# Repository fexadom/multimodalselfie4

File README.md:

# MultimodalSelfie v4
The MultimodalSelfie is a personal multimodal recording device designed for traditional classrooms. The device, owned and operated by the student, sits on top of her desk while recording video, audio, and notes during a class session (as seen in the concept image below); effectively taking a "selfie" of her learning experience.

## Design
This repository contains all the necessary information to construct and test the fourth version of the MultimodalSelfie device (MMSv4 for short). The MMSv4 is based on the [Raspberry Pi Zero W](https://www.raspberrypi.org/products/raspberry-pi-zero-w/) a stripped down version of the Raspberry Pi with wireless connectivity.

Front View | Components | Functionality
--- | --- | ---
 |  | 

### Hardware components
The MMSv4 was built using the following components:

Component | Description | Notes
--- | --- | ---
Raspberry Pi Zero W | 1GHz 64-bit, single-core ARMv8 CPU, 512 MB RAM | 32 GB micro SD
Raspberry Pi Camera | Camera Rev 1.3, 5 megapixeles | Capable of 1080p HD video recording at 30fps
Smart Pen | Equil SmartPen2 | [Manufacturer website](https://www.myequil.com/smartpen2/)
3D Printed Case | Three parts printed using PLA | [STLs](/case)
Pihat | Printed Circuit Board that expands the Raspberry Pi capabilities, it connects to the 40 GPIO port. It has a swith, a LED, and two digital microphones. | [Design files](/pihat)
2 x digital MEMS microphones | The two ICS43432 mics are surface mounted on the Pihat and capable of stereo recording. | [Manufacturer website](https://www.invensense.com/products/digital/ics-43432/)
LiPo battery charger  | SparkFun LiPo Charger Basic - Micro-USB | [Manufacturer website](https://www.sparkfun.com/products/10217)
LiPo battery  | 2000mAh Lithium Ion battery | [Manufacturer website](https://www.sparkfun.com/products/13855)

### Software components
The operating system used is [Raspbian Stretch Lite](https://www.raspberrypi.org/downloads/raspbian/) (Release date 2017-11-29). Video and audio are captured and synchronized using **ffmpeg** and overall synchronization is done with Node-Red:
* [Node-Red flows](/synchronization-software)

## Dependencies
After installing Raspbian Stretch Lite (avoid installing any GUI and unnecessary packages) update as needed with:
```bash
sudo apt-get update
sudo apt-get upgrade
```
then install the following dependencies:

### ffmpeg
For best results, install ffmpeg and its dependencies from the official repository:
```bash
sudo apt-get install ffmpeg
```

### Node-RED
Node-RED is pre-installed in Raspbian Stretch, to enable it:
```bash
sudo systemctl enable nodered.service
```

### Equil
The Equil driver for the SmartPen2 requires Java, to install:
```bash
sudo apt-get install jsvc
```
## Configuration Notes
To use the camera port it is necessary to enable it at boot time, run:
```bash
sudo raspi-config
```
and enable the camera. To map the camera driver to /dev/video0 add this line to /etc/rc.local:
```bash
modprobe bcm2835-v4l2
```
### Installation of synchronization software
Install the contents of the [synchronization software](/synchronization-software) in the folder /opt/recording:
```bash
git clone https://github.com/fexadom/multimodalselfie4.git
cd multimodalselfie4
sudo mv synchronization-software /opt/recording
```
* Copy /opt/recording/node-red/settings.js to ~/.node-red/
* Copy the directory /opt/recording/node-red/node_modules/file-exists to ~/.node-red/node_modules/
* Create a directory "data" in /opt/recording
* Restart the system

### Configure Equil software
Open Equil.sh in /opt/recording/scripts/ and modify as needed:
```bash
JAVA_HOME: Location JAVA JRE
EXEC: Location JSVC
```
### Installation of ICS43432 driver
Use this post: [Add an I2S mic using device tree & simple-audio-card](https://www.raspberrypi.org/forums/viewtopic.php?f=44&t=173640) to install the driver for the ICS43432 digital microphones.

### Configure web server Lighttpd
The web server [Lighttpd](https://www.lighttpd.net/) is necessary to extract all recorded software. To install first remove Apache httpd if installed, then install **lighthttpd** from the official repositoty and enable the service:
```bash
sudo apt-get remove apache2
sudo apt-get install lighttpd
sudo systemctl enable lighttpd.service
```

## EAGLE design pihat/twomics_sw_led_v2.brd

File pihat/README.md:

# Design files for pihat MultimodalSelfie version 4
The pihat for the MMSv4 is a two-layer PCB that connects to the 40-pin GPIO interface of the Raspberry Pi Zero W. It provides the following functionality to the MMSv4:
* Ready LED on GPIO 02
* Push button on GPIO 03
* Two digital MEMS ICS43432 microphones multiplexed together and connected to I2S interface of the Raspberry Pi (GPIO 18-20)

The design files in this repository were made in Eagle v8.

Pihat on device | Pihat front | Pihat back
--- | --- | ---
 |  |

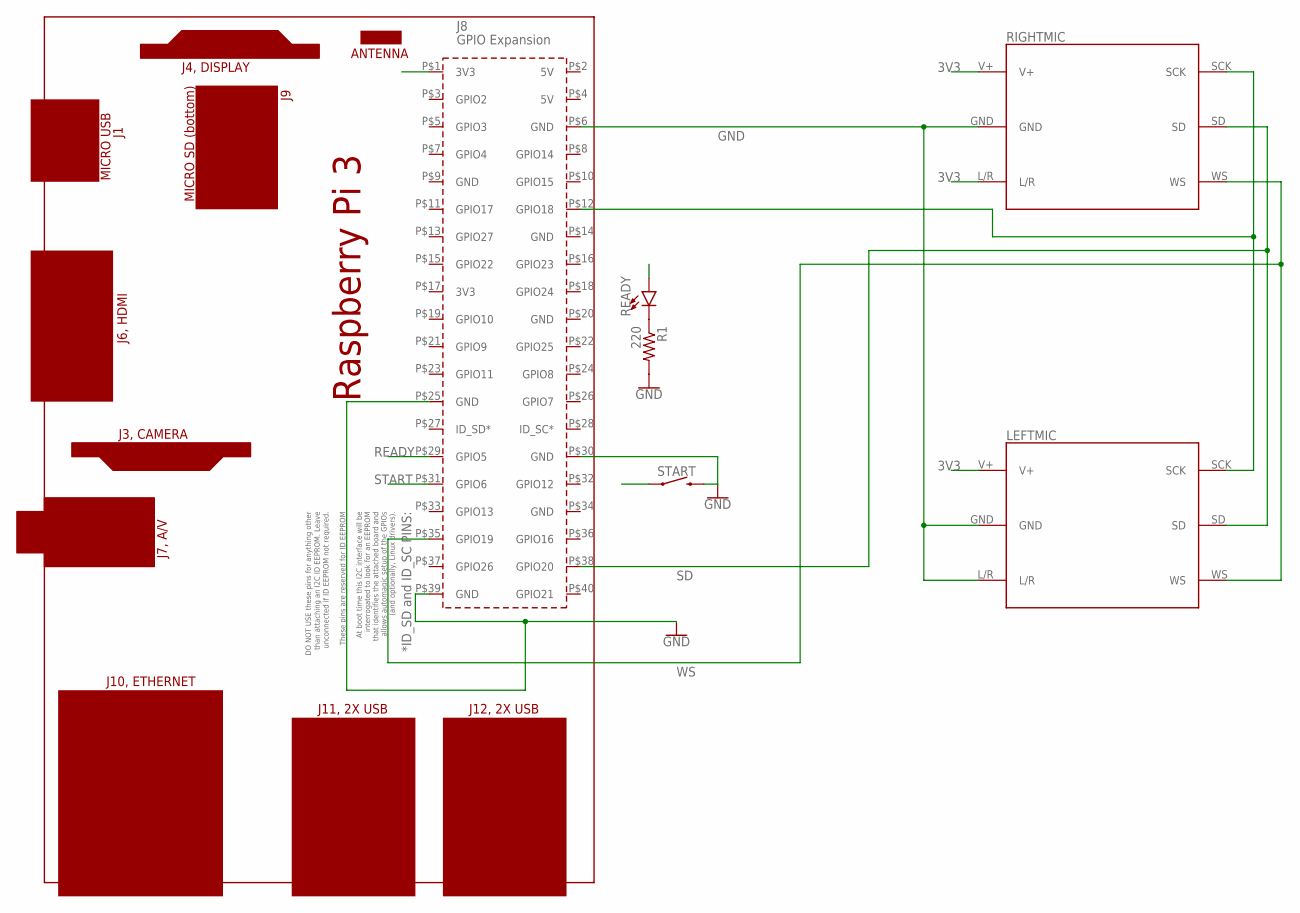
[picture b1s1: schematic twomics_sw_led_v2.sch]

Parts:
LEFTMIC: EMMIC-ICS43432; PTH
PCB1: RPI3_40_PIN; 40_PIN
R1: 220; 0207/7
READY: LED3MM; LED_3MM
RIGHTMIC: EMMIC-ICS43432; PTH
START: MOMENTARY-SWITCH-SPST-PTH-6.0MM; TACTILE_SWITCH_PTH_6.0MM

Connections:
3V3: LEFTMIC.V+, PCB1.P$1 (3V3), RIGHTMIC.L/R, RIGHTMIC.V+
GND: LEFTMIC.GND, LEFTMIC.L/R, PCB1.P$6 (GND), PCB1.P$25 (GND), PCB1.P$30 (GND), PCB1.P$39 (GND), R1.2, RIGHTMIC.GND, START.3 (2)
unnamed: R1.1, READY.K (C)
READY: PCB1.P$29 (GPIO5), READY.A
SCK: LEFTMIC.SCK, PCB1.P$12 (GPIO18), RIGHTMIC.SCK
SD: LEFTMIC.SD, PCB1.P$38 (GPIO20), RIGHTMIC.SD
START: PCB1.P$31 (GPIO6), START.1
WS: LEFTMIC.WS, PCB1.P$35 (GPIO19), RIGHTMIC.WS

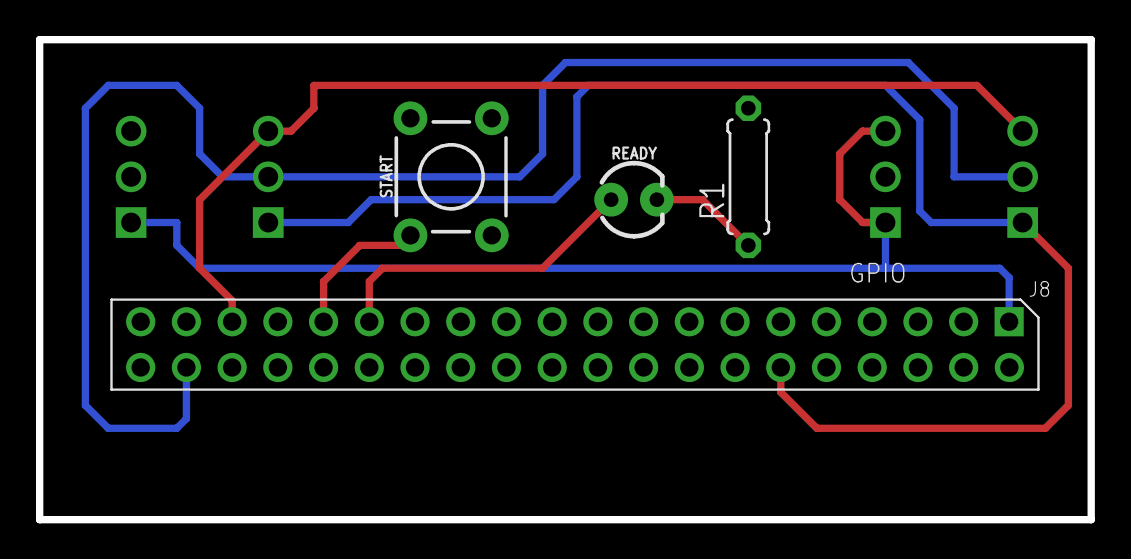
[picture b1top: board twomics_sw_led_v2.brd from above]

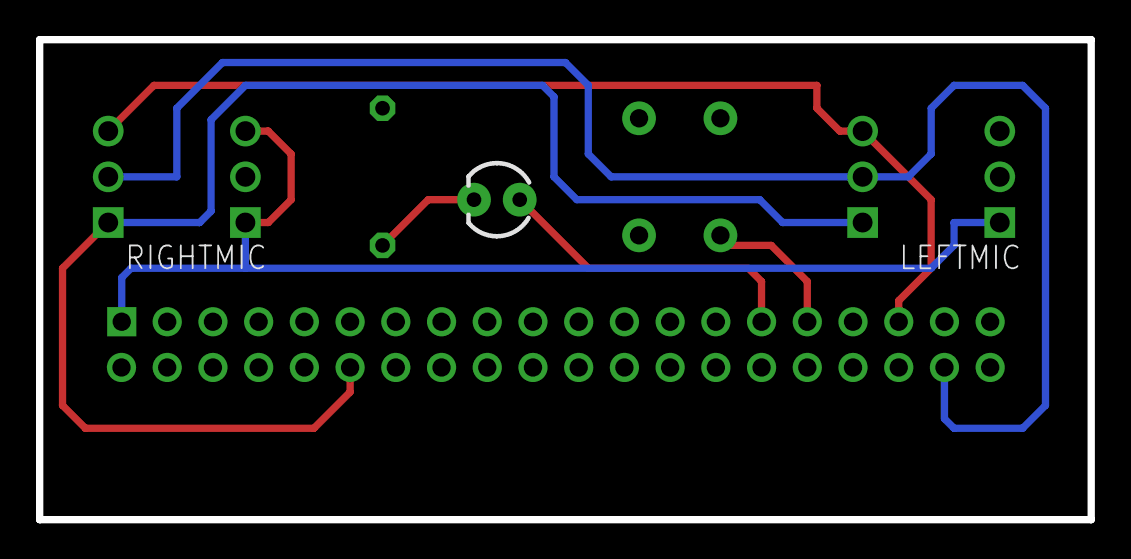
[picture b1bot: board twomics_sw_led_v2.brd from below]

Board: 2 copper layers, 58.4 x 26.7 mm, 6 parts (2 on the bottom side), 8 nets.

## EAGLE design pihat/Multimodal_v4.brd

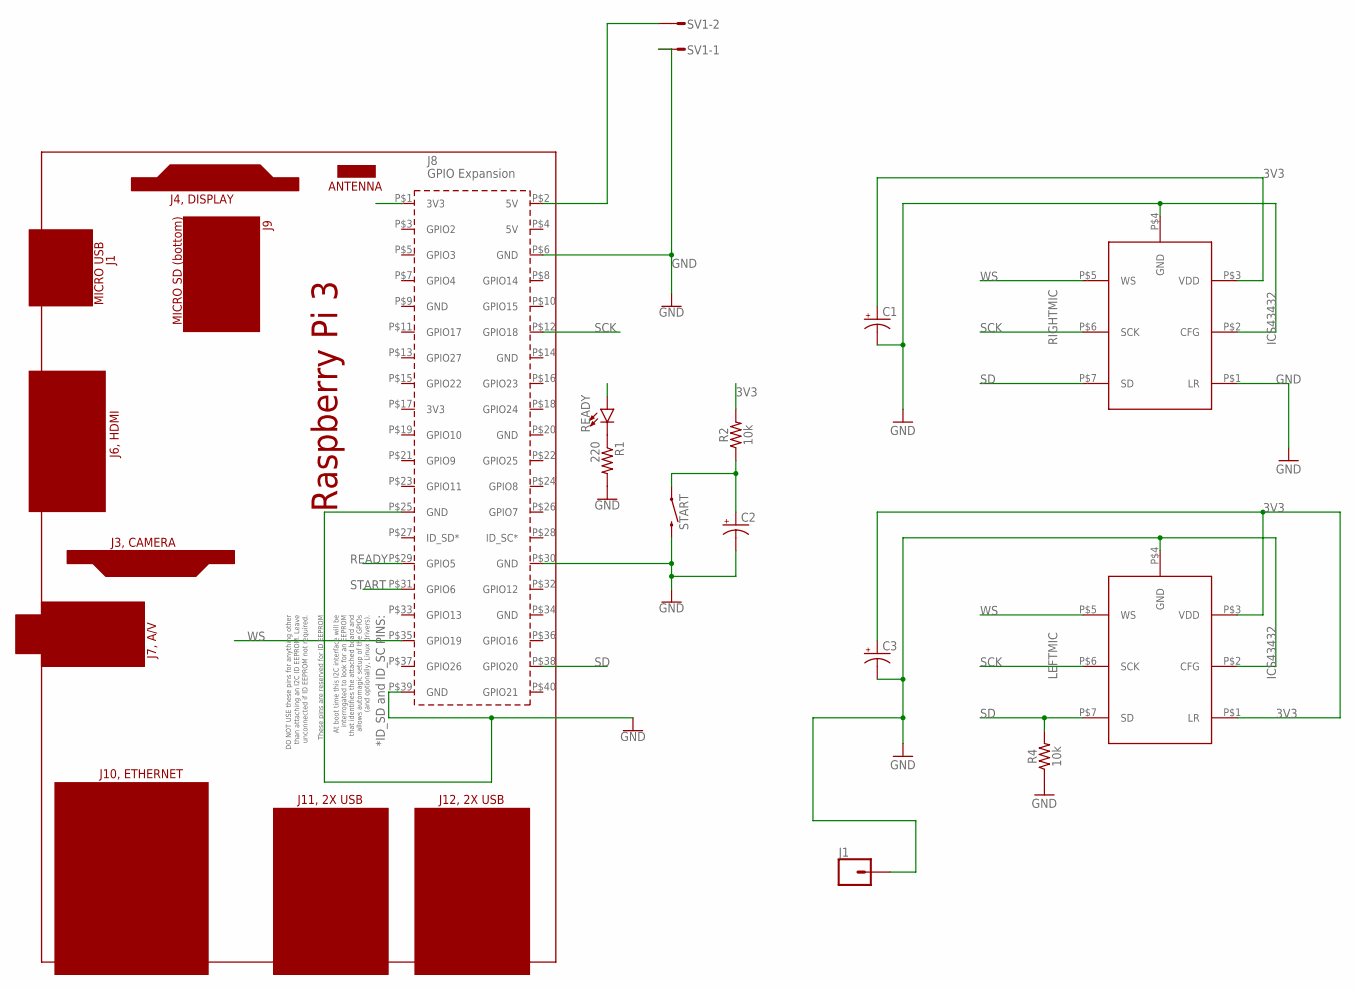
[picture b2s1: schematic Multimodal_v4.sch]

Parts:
C1, C2, C3: CPOL-USE2.5-5; E2,5-5
J1: CONN_01; 1X01
LEFTMIC: ICS43432
PCB1: RPI3_40_PIN; 40_PIN
R1: 220; 0207/7
R2, R4: 10k; AXIAL-0.3-KIT
READY: LED3MM; LED_3MM
RIGHTMIC: ICS43432
START: MOMENTARY-SWITCH-SPST-PTH-6.0MM; TACTILE_SWITCH_PTH_6.0MM
SV1: L02P

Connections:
3V3: C1.+, C3.+, LEFTMIC.P$1 (LR), LEFTMIC.P$3 (VDD), PCB1.P$1 (3V3), R2.P$2 (2), RIGHTMIC.P$3 (VDD)
GND: C1.-, C2.-, C3.-, J1.1, LEFTMIC.P$2 (CFG), LEFTMIC.P$4 (GND), PCB1.P$6 (GND), PCB1.P$25 (GND), PCB1.P$30 (GND), PCB1.P$39 (GND), R1.2, R4.P$1 (1), RIGHTMIC.P$1 (LR), RIGHTMIC.P$2 (CFG), RIGHTMIC.P$4 (GND), START.3 (2), SV1.1
unnamed: R1.1, READY.K (C)
unnamed: PCB1.P$2 (5V), SV1.2
READY: PCB1.P$29 (GPIO5), READY.A
SCK: LEFTMIC.P$6 (SCK), PCB1.P$12 (GPIO18), RIGHTMIC.P$6 (SCK)
SD: LEFTMIC.P$7 (SD), PCB1.P$38 (GPIO20), R4.P$2 (2), RIGHTMIC.P$7 (SD)
START: C2.+, PCB1.P$31 (GPIO6), R2.P$1 (1), START.1
WS: LEFTMIC.P$5 (WS), PCB1.P$35 (GPIO19), RIGHTMIC.P$5 (WS)

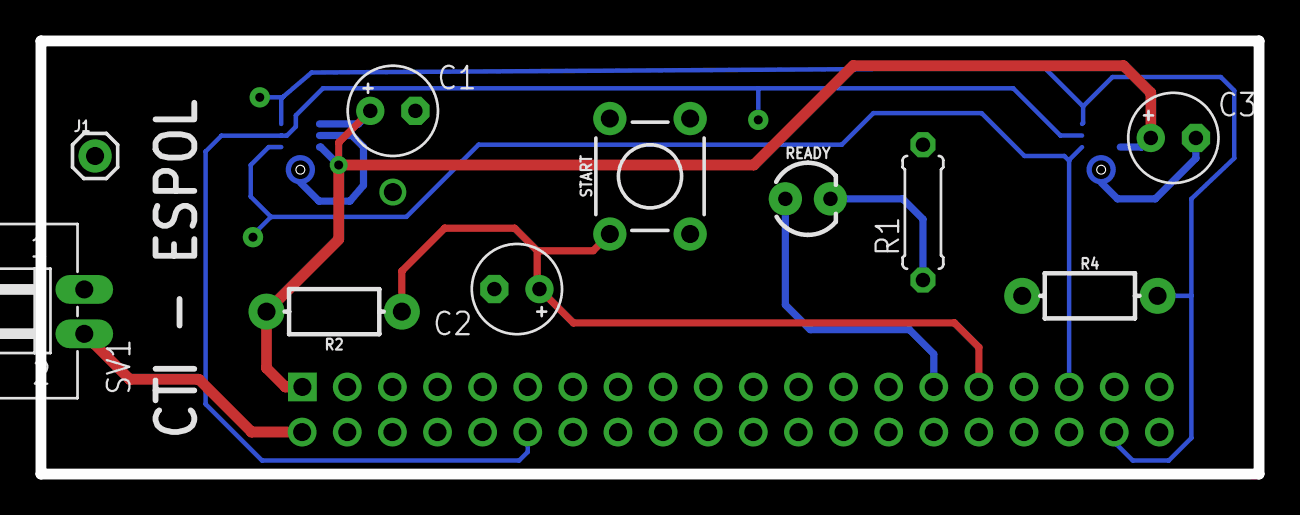
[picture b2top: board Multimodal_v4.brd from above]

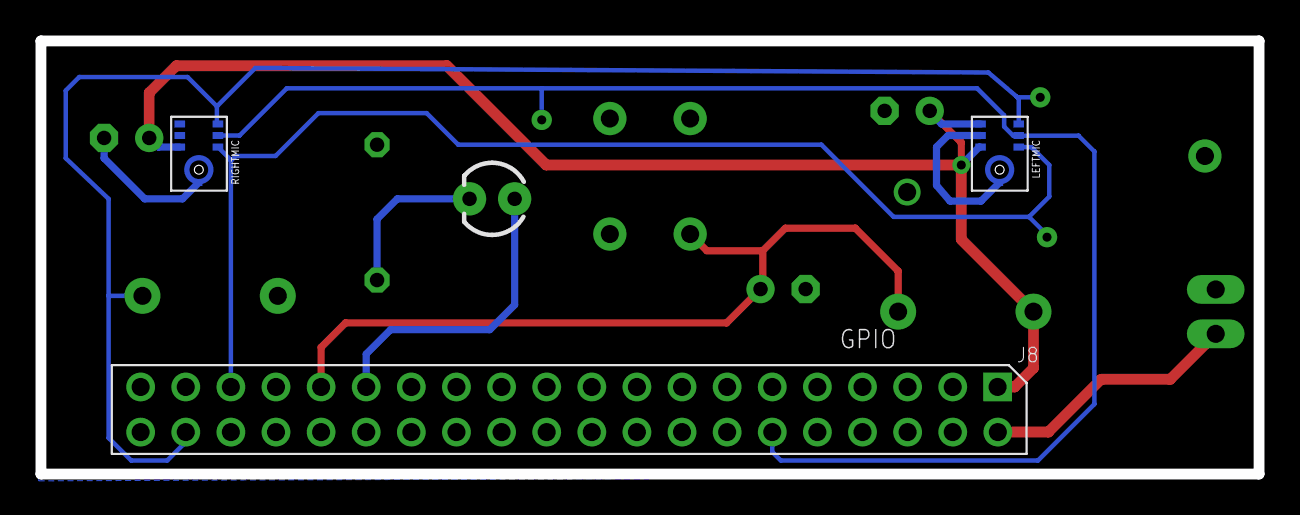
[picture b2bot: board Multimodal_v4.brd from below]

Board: 2 copper layers, 68.6 x 24.4 mm, 13 parts (3 on the bottom side), 9 nets.

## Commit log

2018-03-04 Upload software and hardware files
2018-03-04 Adding case files
2018-03-04 A few syntax errors
2018-03-04 Adding images
2018-03-04 Adding concept image
2018-03-04 Intro README
2018-03-04 Added Design to README
2018-03-04 Components table
2018-03-04 Small corrections
2018-03-04 Software components in README
2018-03-04 Dependencies section
2018-03-04 Installation of sync software section
2018-03-04 Changed files to MMSv4
2018-03-04 Removed old files
2018-03-04 Extra configuration options
2018-03-05 README.md for pihat
2018-03-05 Added pictures to README.md of pihat

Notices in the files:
parts and their libraries:
SparkFun-LED: Licensing: Creative Commons ShareAlike 4.0 International - https://creativecommons.org/licenses/by-sa/4.0
